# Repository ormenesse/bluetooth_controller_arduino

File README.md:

# bluetooth_controller_arduino
Projeto desenvolvido com o objetivo de se criar um controle de video-game bluetooth para android.
Esse controle foi criado com o intuito de funcionar com o microcontrolador Arduino e um .apk desenvolvido para android.
O papel do APK era criar uma interface de teclado que "entendesse" os comandos enviados pelo arduino.

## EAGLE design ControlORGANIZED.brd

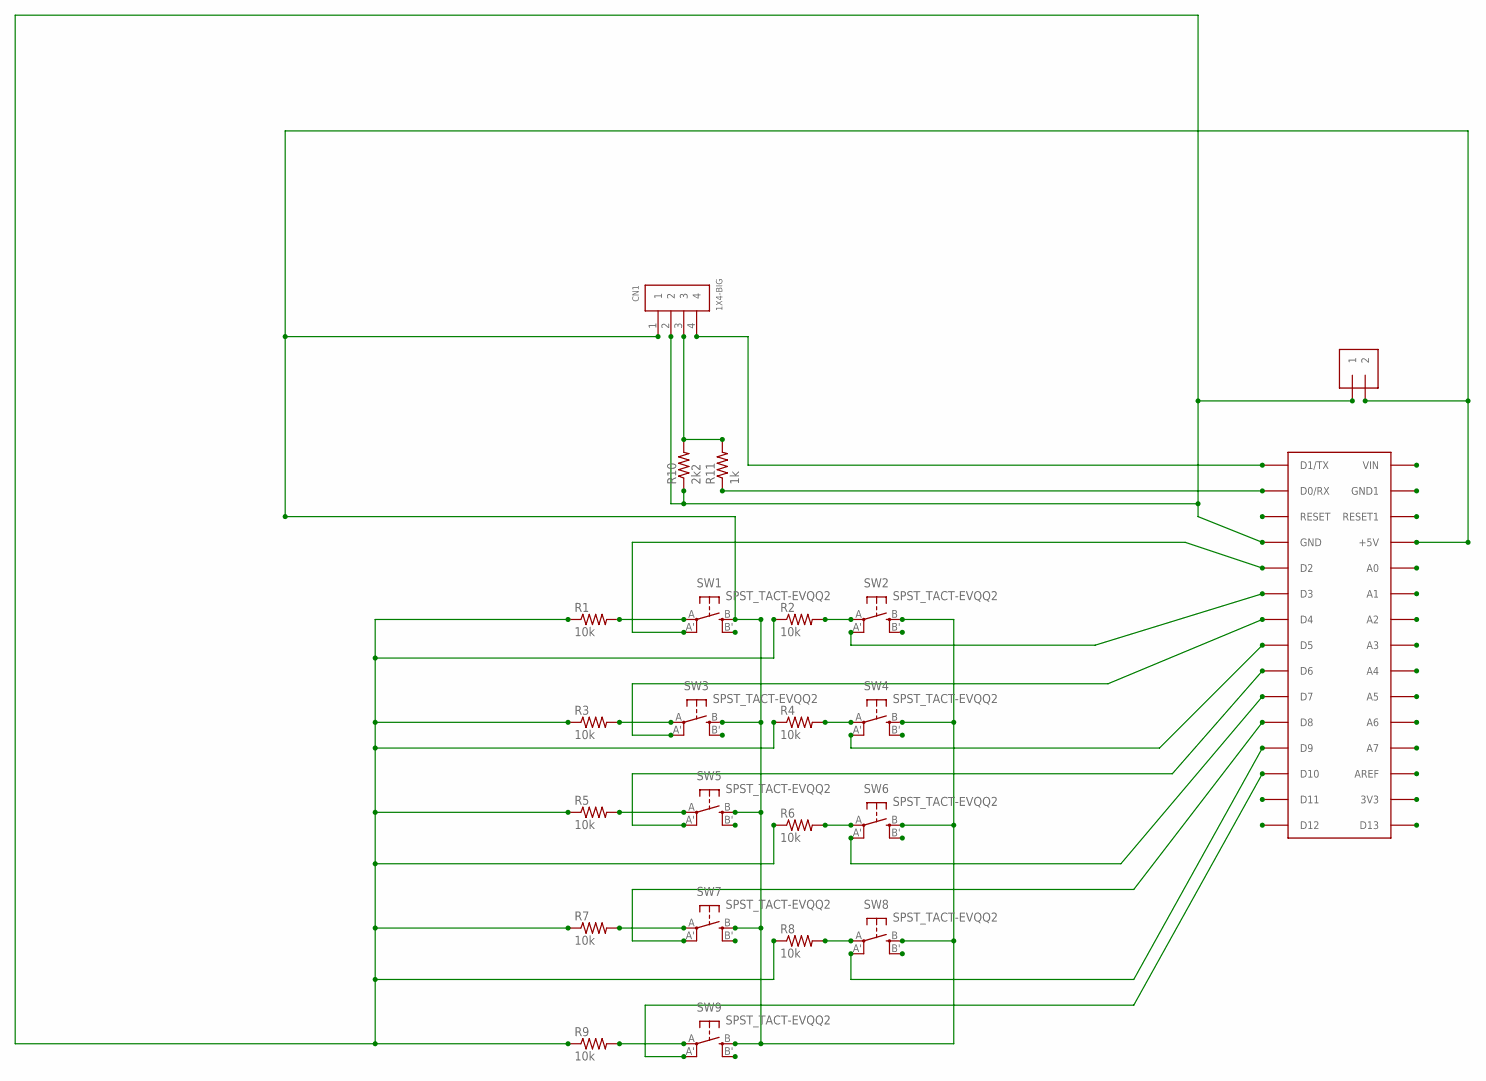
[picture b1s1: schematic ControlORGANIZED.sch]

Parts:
CN1: 1X4-BIG; 1X04-BIG
J1: 1X2-3.5MM
R1, R2, R3, R4, R5, R6, R7, R8, R9: 10k; 0204/7
R10: 2k2; 0204/7
R11: 1k; 0204/7
SW1, SW2, SW3, SW4, SW5, SW6, SW7, SW8, SW9: SPST_TACT-EVQQ2; EVQ-Q2
U$8: ARDUINONANO; PDIP-32

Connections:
unnamed: R2.2, SW2.A
unnamed: R6.2, SW6.A
unnamed: R8.2, SW8.A
unnamed: R7.2, SW7.A
unnamed: R5.2, SW5.A
unnamed: R1.2, SW1.A
unnamed: CN1.1, J1.2, SW1.B (S), SW2.B (S), SW3.B (S), SW4.B (S), SW5.B (S), SW6.B (S), SW7.B (S), SW8.B (S), SW9.B (S), U$8.+5V
unnamed: CN1.3, R10.2, R11.2
unnamed: CN1.2, J1.1, R1.1, R2.1, R3.1, R4.1, R5.1, R6.1, R7.1, R8.1, R9.1, R10.1, U$8.GND
unnamed: R11.1, U$8.D0/RX
unnamed: SW5.A' (P1), U$8.D6
unnamed: SW6.A' (P1), U$8.D7
unnamed: R4.2, SW4.A
unnamed: SW4.A' (P1), U$8.D5
unnamed: SW3.A' (P1), U$8.D4
unnamed: R3.2, SW3.A
unnamed: SW1.A' (P1), U$8.D2
unnamed: SW2.A' (P1), U$8.D3
unnamed: CN1.4, U$8.D1/TX
unnamed: SW7.A' (P1), U$8.D8
unnamed: SW8.A' (P1), U$8.D9
unnamed: R9.2, SW9.A
unnamed: SW9.A' (P1), U$8.D10

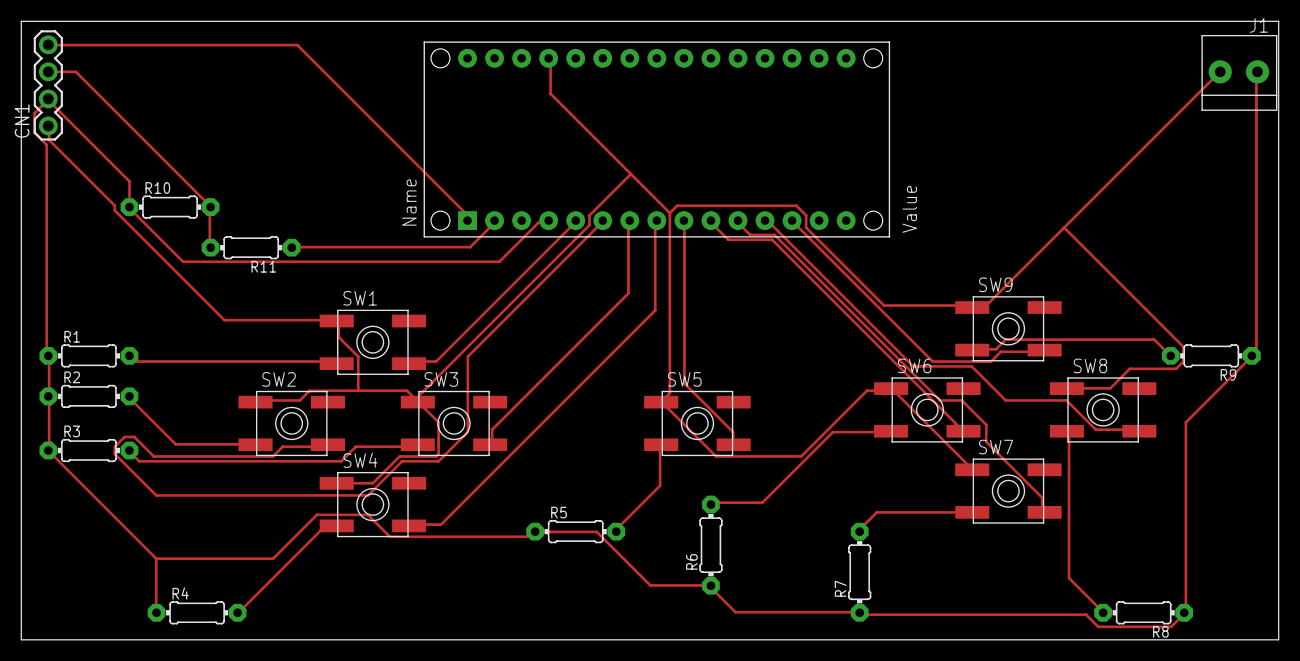
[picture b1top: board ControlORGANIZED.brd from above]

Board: 2 copper layers, 118.1 x 58.1 mm, 23 parts (0 on the bottom side), 23 nets.

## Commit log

2018-01-11 Add files via upload
    Esquemas SMD do controle bluetooth.
    Lembrando que esse projeto foi pensado para um arduino nano.
